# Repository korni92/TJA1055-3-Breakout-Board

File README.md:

# TJA1055/3 Breakout Board — Rev 1.1

An open-hardware breakout for **low-speed fault-tolerant CAN (ISO 11898-3)**, built around
the NXP **TJA1055T/3** transceiver with an optional on-board Microchip **MCP2515** CAN
controller. Runs directly from **3.3 V hosts** — Raspberry Pi, ESP32 — with no level
shifters.

> ⚠️ **Use at your own risk.** This is a bench and diagnostic tool, not a qualified ECU.
> Only the 12 V rail is reverse-polarity protected; there is no fuse and no bus transient
> suppression. Working on a live vehicle bus can disturb or damage control units.

---

## Quick start

If you just want CAN and don't care about the transceiver's power-management features:

1. Fit both **SWITCH** jumpers (J10, J11). Without them STB and EN are pulled low
   internally and the transceiver sits in sleep — the board looks dead.
2. Leave both **TERM** jumpers (J6, J7) open when connecting to a vehicle. The bus is
   already terminated.
3. Set **J2 and J4 both to the right** for the on-board MCP2515, or both to the left to
   drive TXD/RXD from your own controller via J1 pins 1 and 2.
4. Feed GND, 12 V, 5 V and 3.3 V into J1.

---

## Contents

- [Features](#features)
- [What changed in Rev 1.1](#what-changed-in-rev-11)
- [Block diagram](#block-diagram)
- [Connectors](#connectors)
- [Jumpers](#jumpers)
- [Operating modes](#operating-modes)
- [Bus termination](#bus-termination)
- [Power supply](#power-supply)
- [Local wake-up](#local-wake-up)
- [Raspberry Pi](#raspberry-pi)
- [ESP32](#esp32)
- [Bit timing at 8 MHz](#bit-timing-at-8-mhz)
- [Bill of materials](#bill-of-materials)
- [Assembly](#assembly)
- [Known limitations](#known-limitations)
- [Design notes](#design-notes)
- [License](#license)

---

## Features

- **TJA1055T/3** fault-tolerant CAN transceiver: up to 125 kBd, automatic single-wire
  fallback on bus faults, ±58 V bus robustness, ±8 kV HBM ESD on CANH/CANL/RTH/RTL
- **Native 3.3 V interface.** The `/3` variant has open-drain RXD and ERR outputs; the
  required pull-ups (R5, R1) are on the board
- **Two ways to reach the bus**, jumper-selectable:
  - the on-board **MCP2515** over SPI — for Raspberry Pi, or an ESP32 with no free TWAI
    controller
  - an **external CAN controller** wired straight to TXD/RXD — e.g. the ESP32 TWAI
    peripheral
- **Switchable termination**: ~547 Ω or 4.7 kΩ per bus line
- **Local wake-up input** for waking the transceiver out of standby or sleep
- **INH output** for enabling an external regulator
- Screw terminal and pin header in parallel for the CAN bus
- Reverse-polarity protection on the 12 V input

## What changed in Rev 1.1

| Change | Reason |
|---|---|
| **R13 (1 kΩ)** in series with pin BAT | Automotive transient protection; NXP AH0801 §4.2.5 recommends 1–2 kΩ |
| **C7 (10 nF)** from BAT to GND | Transient suppression close to the BAT pin |
| **R14 (47 kΩ) / R4 (10 kΩ)** wake network, **J12** header | Local wake-up per AH0801 §4.2.2 — R14 pulls to battery, R4 limits current into the pin |
| **D1 (PMEG4010CEH)** on the 12 V input | Reverse-polarity blocking for the whole battery branch |
| **C8 (100 µF alu-polymer)** on the 5 V rail | Buffers the transceiver's peak current during bus faults |
| **INH** on J1 with **R15 (100 kΩ)** pull-down | Lets the board control an external regulator |
| **J10/J11 + R16/R17 (10 kΩ)** SWITCH jumpers | Optional strap of STB and EN to 3.3 V |
| **R10/R11 raised to 620 Ω** | Keeps the parallel termination safely above the 500 Ω minimum |
| J5 folded into J1, J1 grown to 1×10 | Fewer connectors, RX/TX now on the main header |

Rev 1.0 ran in-vehicle with both a Raspberry Pi and an ESP32.

## Block diagram

```
  J1.4 BAT ─[D1]─┬──────────────────────────────────────────────┐
                 │                                              │
                 ├─[R13 1k]──┬── BAT ┐                   [R14 47k]
                 │        [C7 10n]   │                          │
                 │           │       │      ┌── RTH ─[R9 4k7]───┴──┬── CANH ── HI
  J1.5 +5V ──────┴───────────┴── VCC │      │      [J6+R10 620] ───┘
              [C1 100n, C8 100u]     │      │
                                     │      ├── RTL ─[R12 4k7]──┬── CANL ── LO
  J1.2 TX ──┬───────────────────── TXD      │      [J7+R11 620] ─┘
            │   (J2/J4: MCP or external)    │
  J1.1 RX ──┴──[R5 4k7 → 3V3]────────── RXD │      C5/C6 100 pF: CANH/CANL → GND
  J1.10 ERR ───[R1 4k7 → 3V3]────────── ERR │
  J1.8 STB ─┬────────────────────────── STB │      STB/EN have internal pull-down
  J1.9 EN  ─┤                           EN  │      current sources — floating means
            └─[J10/J11 + R16/R17 10k → 3V3] │      sleep, not normal mode
  J1.7 INH ─┬────────────────────────── INH │
         [R15 100k]                         │
                                            │
  J12 ── button ── GND ───────[R4 10k]── WAKE
                                            │
  J3 SPI ── MCP2515 (3V3, 8 MHz) ── TXCAN/RXCAN ── J2/J4
```

## Connectors

All through-hole positions take standard 2.54 mm male pin headers.

### J1 — power, control and external CAN controller (1×10)

| Pin | Silk | Signal | Direction | Notes |
|---|---|---|---|---|
| 1 | `RX` | RXD | out | from the transceiver to your controller (J2 set left) |
| 2 | `TX` | TXD | in | from your controller to the transceiver (J4 set left) |
| 3 | `GND` | GND | — | must be bonded to vehicle ground |
| 4 | `BAT` | +12 V | in | battery feed, behind D1. 5–40 V is within the transceiver's rating |
| 5 | `5V` | +5 V | in | transceiver V<sub>CC</sub> — see [Power supply](#power-supply) |
| 6 | `3V3` | +3.3 V | in | MCP2515 supply and reference for every pull-up on the board |
| 7 | `INH` | INH | out | regulator enable, **battery-referenced** |
| 8 | `STB` | STB | in | mode pin, active low |
| 9 | `EN` | EN | in | mode pin |
| 10 | `ERR` | ERR | out (open drain) | error / wake-up / power-on flag, active low, pulled up to 3V3 |

> ⚠️ **INH is not a GPIO.** It is a high-side switch to BAT and outputs V<sub>BAT</sub> when
> active. Do not connect it to a 3.3 V input without level shifting.

### J3 — SPI to the MCP2515 (1×5)

| Pin | Silk | Signal | Pi (BCM) | ESP32 (example) |
|---|---|---|---|---|
| 1 | `CS` | CS | GPIO8 (CE0) | GPIO5 |
| 2 | `SO` | MISO | GPIO9 | GPIO19 |
| 3 | `SI` | MOSI | GPIO10 | GPIO23 |
| 4 | `SCK` | SCK | GPIO11 | GPIO18 |
| 5 | `INT` | INT | GPIO25 | GPIO4 |

### J8 / J9 — CAN bus

J8 is a screw terminal, J9 a pin header, wired in parallel so the board can be daisy-chained.
Both are marked `HI` and `LO` on the silkscreen, and **viewed from above, HI and LO are on
the same side of both connectors** — go by the silkscreen, not by pin number

| Silk | Signal |
|---|---|
| `HI` | CANH |
| `LO` | CANL |

> Fault-tolerant CAN has **no** 120 Ω resistor across the pair. Plugging in a high-speed CAN
> tool with its 120 Ω termination forces the whole bus into single-wire mode.

### J12 — local wake-up input (1×1)

Connect a button or contact between J12 and ground; J1 pin 3 is convenient. See
[Local wake-up](#local-wake-up).

## Jumpers

| Ref | Silk | Function | Default |
|---|---|---|---|
| J4 | `RX/TX ↦ … ↦ MCP2515` | TXD source: left = J1.2, right = MCP2515 | right |
| J2 | `RX/TX ↦ … ↦ MCP2515` | RXD destination: left = J1.1, right = MCP2515 | right |
| J6 | `TERM` | 620 Ω in parallel on RTH (CANH side) | open |
| J7 | `TERM` | 620 Ω in parallel on RTL (CANL side) | open |
| J10 | `SWITCH` `GPIO`/`ON` | straps STB to 3.3 V through R16 (10 kΩ) | fitted |
| J11 | `SWITCH` `GPIO`/`ON` | straps EN to 3.3 V through R17 (10 kΩ) | fitted |

### J2 / J4 — controller select

The two 1×3 headers sit one above the other and are mirrored, so the pads line up in three
columns regardless of pin numbering:

| Column | Upper row (J2, RXD) | Lower row (J4, TXD) |
|---|---|---|
| left | J1.1 RX | J1.2 TX |
| middle | transceiver RXD | transceiver TXD |
| right | MCP2515 RXCAN | MCP2515 TXCAN |

Move both jumpers to the same side. With neither fitted, TXD floats — the TJA1055 has an
internal pull-up on TXD, so the bus stays recessive and the board will not disturb traffic,
but it will not transmit or receive either.

### J10 / J11 — SWITCH

STB and EN have internal pull-down current sources of roughly 10 µA. Left alone the
transceiver falls into a low-power mode on its own, which is the fail-safe behaviour NXP
intends. Fitting a SWITCH jumper straps the pin to 3.3 V through 10 kΩ, so the board comes
up in normal mode without the host driving anything.

The 10 kΩ matters: with a jumper fitted **and** a GPIO connected, the GPIO still wins — it
only has to sink 330 µA — so you keep full mode control without a short between the GPIO
and the 3.3 V rail. You never have to pull the jumper.

> Fitted jumpers keep the transceiver in normal mode permanently, drawing several mA.
> On permanent battery power that will slowly discharge the vehicle battery.

## Operating modes

| STB (J1.8) | EN (J1.9) | Mode |
|---|---|---|
| 1 | 1 | **Normal** — transmit and receive; ERR reports bus faults |
| 1 | 0 | Power-on standby — ERR reports the power-on flag |
| 0 | 1 | Go-to-sleep — hold for at least 50 µs |
| 0 | 0 | Standby / sleep — RXD and ERR report the wake-up flag |

INH is active in every mode except sleep.

## Bus termination

Fault-tolerant CAN uses **distributed** termination: every node carries one resistor from
RTH to CANH and one from RTL to CANL.

- Per node: **500 Ω to 6 kΩ**
- Across the whole network: about **100 Ω per line**

| TERM jumpers | R<sub>RTH</sub> / R<sub>RTL</sub> | When |
|---|---|---|
| open | 4.7 kΩ | **default in a vehicle** — the bus is already terminated |
| fitted | 4.7 kΩ ∥ 620 Ω ≈ 547 Ω | bench setup where this board is the terminating (gateway) node |

Set J6 and J7 together — the network only stays balanced if both lines are terminated
symmetrically. Two boards on a bench with both fitted gives 547 Ω ∥ 547 Ω ≈ 274 Ω, which
works but is higher impedance than the nominal design point.

## Power supply

There is no regulator on the board. All three rails come in through J1.

| Rail | Load | Requirement |
|---|---|---|
| BAT (12 V) | pin BAT via D1 and R13, plus R14 and R15 | tens of µA in low-power mode, ~1.7 mA worst case |
| +5 V | transceiver V<sub>CC</sub> | ~38 mA average, **peaks to 135 mA** for up to 6 bit times during a bus short |
| +3.3 V | MCP2515 and all pull-ups | ~10 mA |

C8 buffers the 5 V peaks. NXP's worst case for a separately supplied transceiver is roughly
25 µF at 125 kBd and 95 µF at 33.3 kBd, assuming a regulator that cannot respond inside the
fault window; a real supply needs less.

D1 and R13 together drop up to about 2 V at worst-case current, so the board needs roughly
7.5 V at J1.4 to keep BAT above its 5 V minimum. That only matters during cranking.

## Local wake-up

```
BAT ──[R14 47k]──┬──[R4 10k]── WAKE (pin 7)
                 │
                 └── J12 ── button ── GND
```

With nothing on J12, WAKE sits at battery level through R14 and R4 — the inactive state.
Pulling J12 to ground wakes the transceiver.

- **WAKE is edge-sensitive in both directions.** A button generates a wake-up event on press
  *and* on release.
- R14 sets the contact wetting current to roughly 255 µA at 12 V, enough for ordinary
  mechanical contacts.
- R4 is the protection resistor required by AH0801 §4.2.2. It limits current into the pin if
  the board loses its ground connection while the button is still tied to vehicle ground.

## Raspberry Pi

Set J2 and J4 to the right (MCP2515), fit both SWITCH jumpers.

`/boot/firmware/config.txt`:

```ini
dtparam=spi=on
dtoverlay=mcp2515-can0,oscillator=8000000,interrupt=25,spimaxfrequency=10000000
```

After rebooting:

```bash
sudo apt install can-utils
sudo ip link set can0 up type can bitrate 33333 restart-ms 100
candump can0
cansend can0 123#DEADBEEF
```

> `oscillator` must be **8000000**. Passing 16000000 by mistake halves every bit rate you
> configure and nothing will decode.

## ESP32

### Option A — MCP2515 over SPI

Set J2/J4 to the right. Use any MCP2515 library, configured for an **8 MHz** crystal.

### Option B — the ESP32's own TWAI controller

Set J2/J4 to the left and wire J1.1 (RX) and J1.2 (TX) to your chosen GPIOs.

```c
twai_general_config_t g = TWAI_GENERAL_CONFIG_DEFAULT(TX_GPIO, RX_GPIO, TWAI_MODE_NORMAL);
twai_timing_config_t  t = TWAI_TIMING_CONFIG_125KBITS();
twai_filter_config_t  f = TWAI_FILTER_CONFIG_ACCEPT_ALL();
```

ESP-IDF has no preset for 33.333 kBd — set the timing struct manually.

## Bit timing at 8 MHz

t<sub>Q</sub> = 2 × (BRP+1) / f<sub>OSC</sub>

| Bit rate | BRP | t<sub>Q</sub> | TQ per bit | Typical use |
|---|---|---|---|---|
| 33.333 kBd | 7 | 2.00 µs | 15 | GM low-speed CAN |
| 50 kBd | 4 | 1.25 µs | 16 | |
| 83.333 kBd | 2 | 0.75 µs | 16 | |
| 100 kBd | 4 | 1.25 µs | 8 | |
| 125 kBd | 1 | 0.50 µs | 16 | ISO 11898-3 maximum |

All of these are exact at 8 MHz — no timing error.

## Bill of materials

Passives are 0603. LCSC part numbers are the ones used for the JLCPCB assembly order.

| Ref | Value / part | Package | LCSC | Notes |
|---|---|---|---|---|
| IC1 | **NXP TJA1055T/3/1J** | SO14 | C2998207 | **The `/3` suffix is mandatory.** The plain TJA1055T drives RXD and ERR push-pull to 5 V and will damage 3.3 V GPIOs |
| U1 | Microchip MCP2515-I/SO | SOIC-18W | C12368 | |
| Y1 | YXC X49SM8MSD2SC, 8 MHz | HC-49S-SMD | C12674 | C<sub>L</sub> = 20 pF, ±20 ppm, ESR 70 Ω |
| C1, C2 | 100 nF X7R | 0603 | C14663 | V<sub>CC</sub> and V<sub>DD</sub> decoupling |
| C3, C4 | 22 pF C0G | 0603 | C1653 | see [Known limitations](#known-limitations) |
| C5, C6 | 100 pF C0G | 0603 | C14858 | CANH/CANL to GND, EMC |
| C7 | 10 nF 50 V X7R | 0603 | C57112 | BAT transient suppression |
| C8 | 100 µF 16 V alu-polymer | D6.3 × L5.8 | C5246523 | 5 V bulk, polarised |
| D1 | Nexperia PMEG4010CEH | SOD-123F | C193342 | reverse-polarity blocking |
| R1, R5, R9, R12 | 4.7 kΩ 1 % | 0603 | C23162 | ERR/RXD pull-ups and RTH/RTL termination |
| R4, R6, R7, R8, R16, R17 | 10 kΩ 1 % | 0603 | C25804 | WAKE series, MCP2515 pull-ups, SWITCH straps |
| R10, R11 | 620 Ω 1 % | 0603 | C23220 | switched termination |
| R13 | 1 kΩ 1 % | 0603 | C21190 | BAT series resistor |
| R14 | 47 kΩ 1 % | 0603 | C25819 | WAKE pull-up to battery |
| R15 | 100 kΩ 1 % | 0603 | C25803 | INH pull-down |
| J1 | 1×10 pin header | 2.54 mm | C5156617 | |
| J2, J4 | 1×3 pin header | 2.54 mm | C49257 | |
| J3 | 1×5 pin header | 2.54 mm | C5156614 | |
| J6, J7, J9, J10, J11 | 1×2 pin header | 2.54 mm | C5360898 | |
| J8 | TE 282834-2 screw terminal | 2.54 mm | C592983 | |
| J12 | 1×1 pin header | 2.54 mm | — | not carried by JLCPCB, fit by hand |

There are deliberately **no resistors permanently tied to STB and EN**. The transceiver
provides internal pull-down current sources, which is the fail-safe behaviour NXP intends;
R16/R17 are only in circuit when the SWITCH jumpers are fitted.

## Assembly

All SMD parts are on the top side and can be ordered pre-assembled. Every through-hole
part — the pin headers, the screw terminal and the single-pin wake header — is fitted by
hand.

You also need five 2.54 mm jumper shunts: two for J2/J4, two for the SWITCH positions, and
optionally two more if you use the TERM jumpers.

## Known limitations

1. **No fuse and no load-dump clamp** on the 12 V input. D1 blocks reverse polarity and R13
   limits current into the BAT pin, but for permanent in-vehicle use add an external fuse or
   PTC, and consider an SMBJ26A/SMBJ30A TVS after D1.
2. **No bus ESD/transient diodes.** The transceiver's own ±8 kV HBM rating covers bench and
   diagnostic use; for harsher environments NXP suggests a PESD1CAN close to the connector.
3. **The oscillator is deliberately under-loaded.** The crystal specifies C<sub>L</sub> =
   20 pF, which would call for roughly 33 pF per leg. C3/C4 are 22 pF instead — the value
   Microchip tested at 8 MHz (DS20001801K Table 8-2) — so the crystal sees about 15 pF and
   runs some 75 ppm fast. The MCP2515 allows 1.7 % node-to-node oscillator variation, so
   that is two orders of magnitude inside tolerance, and under-loading buys start-up margin
   and lower crystal drive. Do not "correct" this to 33 pF.
4. **J1 is an unkeyed pin header.** Plugging it in backwards puts 12 V on the 3.3 V rail.
5. **No sleep-capable power path by default.** INH is available on J1, but the board has no
   regulator of its own, so a full sleep setup needs external hardware.
6. **J6 and J7 share one `TERM` label** and are not individually marked HI and LO. They are
   always set together, so this is cosmetic.

## Design notes

- NXP **TJA1055** product data sheet (Rev. 5, 2013). For the `/3` variant, RXD and ERR are
  open-drain and require external pull-ups.
- NXP **AH0801 — Application Hints TJA1055T** (Rev. 1.5, 2016). The basis for R13/C7
  (§4.2.5), the wake circuit (§4.2.2), the µC interface including the pull-up sizing
  calculation (§4.2.4), bus capacitors (§6.1.3) and termination (§9.1). The design checklist
  in §7 is worth walking through before any layout review.
- Microchip **MCP2515** data sheet (DS20001801K). §8 and Table 8-2 give the tested
  oscillator load capacitors; §5.6 states the 1.7 % oscillator tolerance. The TXnRTS pins
  have internal 100 kΩ pull-ups and may be left open.

Layout points from the NXP checklist that apply here: keep CANH and CANL short, parallel and
symmetrical on the way to the connector; put decoupling capacitors right at the supply pins;
keep a continuous ground plane; keep the controller-to-transceiver run short.

## License

| Part | License |
|---|---|
| Hardware — schematic, layout, gerbers | [CERN-OHL-S-2.0](https://cern-ohl.web.cern.ch/) |
| Example code | [MIT](LICENSE) |
| Documentation | [CC-BY-4.0](https://creativecommons.org/licenses/by/4.0/) |

---

*Rev 1.1 — drawn in KiCad 10.0.6*

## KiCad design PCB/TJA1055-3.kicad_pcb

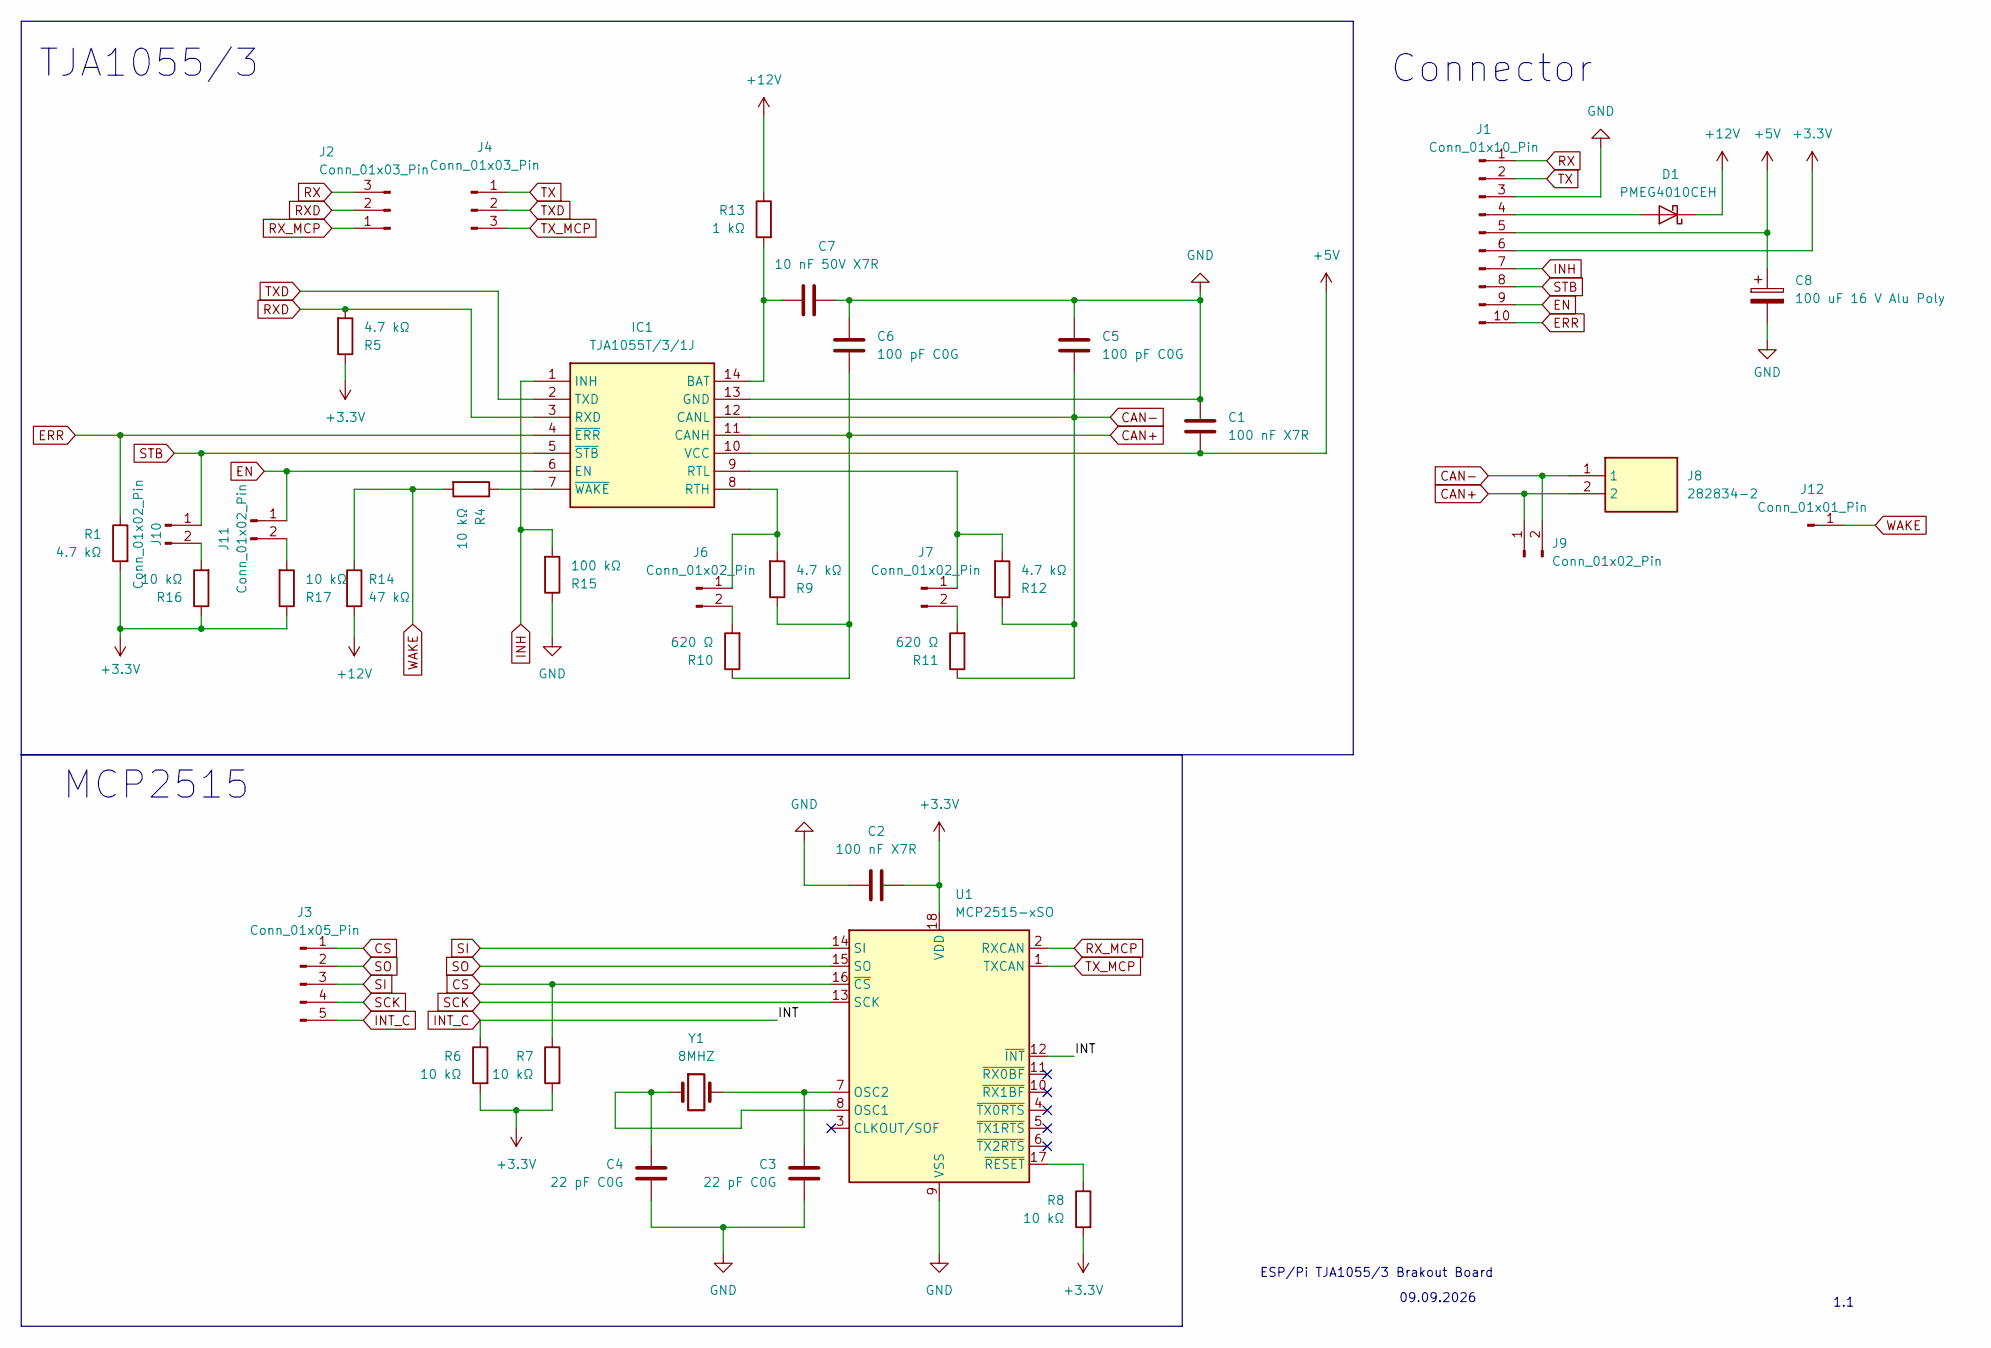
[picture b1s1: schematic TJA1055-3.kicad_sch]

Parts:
C1, C2: 100 nF X7R; C_0603_1608Metric
C3, C4: 22 pF C0G; C_0603_1608Metric
C5, C6: 100 pF C0G; C_0603_1608Metric
C7: 10 nF 50V X7R; C_0603_1608Metric
C8: 100 uF 16 V Alu Poly; CP_Elec_6.3x5.8
D1: PMEG4010CEH; D_SOD-123F
IC1: TJA1055T/3/1J; SOIC127P600X175-14N; Mouser Part Number 771-TJA1055T3C518
J1: Conn_01x10_Pin; PinSocket_1x10_P2.54mm_Vertical
J2, J4: Conn_01x03_Pin; PinSocket_1x03_P2.54mm_Vertical
J3: Conn_01x05_Pin; PinSocket_1x05_P2.54mm_Vertical
J6, J7, J9, J10, J11: Conn_01x02_Pin; PinSocket_1x02_P2.54mm_Vertical
J8: 282834-2; 282834-2_1; Mouser Part Number 571-282834-2
J12: Conn_01x01_Pin; PinHeader_1x01_P2.54mm_Vertical
R1, R5, R9, R12: 4.7 kΩ; R_0603_1608Metric
R4, R6, R7, R8, R16, R17: 10 kΩ; R_0603_1608Metric
R10, R11: 620 Ω; R_0603_1608Metric
R13: 1 kΩ; R_0603_1608Metric
R14: 47 kΩ; R_0603_1608Metric
R15: 100 kΩ; R_0603_1608Metric
U1: MCP2515-xSO; SOIC-18W_7.5x11.6mm_P1.27mm
Y1: 8MHZ; Crystal_SMD_HC49-SD; Manufacturer_Part_Number X49SM8MSD2SC; LCSC Part # C12674

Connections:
+3.3V: C2.1, J1.6, R1.2, R5.1, R6.2, R7.2, R8.2, R16.1, R17.1, U1.18 (VDD)
+5V: C1.2, C8.1, IC1.10 (VCC), J1.5
+12V: D1.1 (K), R13.1, R14.2
CAN+: C6.2, IC1.11 (CANH), J8.2, J9.1, R9.1, R10.1
CAN-: C5.2, IC1.12 (CANL), J8.1, J9.2, R11.1, R12.1
CS: J3.1, R7.1, U1.16 (~CS)
EN: IC1.6 (EN), J1.9, J11.1
ERR: IC1.4 (~ERR), J1.10, R1.1
GND: C1.1, C2.2, C3.2, C4.2, C5.1, C6.1, C7.1, C8.2, IC1.13 (GND), J1.3, R15.1, U1.9 (VSS)
INH: IC1.1 (INH), J1.7, R15.2
INT_C: J3.5, R6.1, U1.12 (~INT)
unnamed: D1.2 (A), J1.4
unnamed: C7.2, IC1.14 (BAT), R13.2
unnamed: IC1.8 (RTH), J6.1, R9.2
unnamed: IC1.9 (RTL), J7.1, R12.2
unnamed: IC1.7 (~WAKE), R4.1
unnamed: J6.2, R10.2
unnamed: J7.2, R11.2
unnamed: J10.2, R16.2
unnamed: J11.2, R17.2
unnamed: C4.1, U1.8 (OSC1), Y1.1
unnamed: C3.1, U1.7 (OSC2), Y1.2
unnamed: R8.1, U1.17 (~RESET)
RX: J1.1, J2.3
RXD: IC1.3 (RXD), J2.2, R5.2
RX_MCP: J2.1, U1.2 (RXCAN)
SCK: J3.4, U1.13 (SCK)
SI: J3.3, U1.14 (SI)
SO: J3.2, U1.15 (SO)
STB: IC1.5 (~STB), J1.8, J10.1
TX: J1.2, J4.1
TXD: IC1.2 (TXD), J4.2
TX_MCP: J4.3, U1.1 (TXCAN)
WAKE: J12.1 (Pin_1_1), R4.2, R14.1

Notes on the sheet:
TJA1055/3
1.1
Connector
09.09.2026
ESP/Pi TJA1055/3 Brakout Board
MCP2515

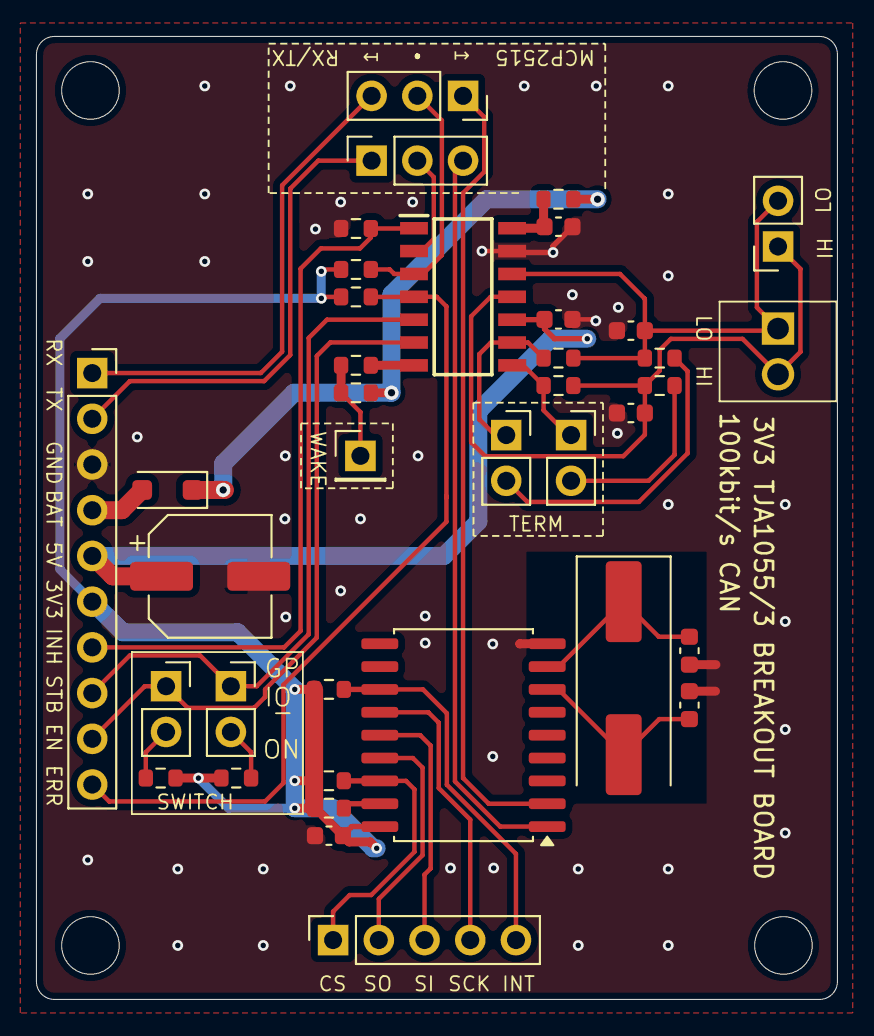
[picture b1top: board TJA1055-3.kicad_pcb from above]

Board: 2 copper layers, 44.5 x 53.5 mm, 38 parts (0 on the bottom side), 34 nets.
